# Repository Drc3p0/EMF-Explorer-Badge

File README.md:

# EMF Explorer Badge

Explore the electromagnetic frequencies around you with the [EMF Explorer badge](https://emfexplorer.space), created by Darcy Neal of [SporkLogic](https://sporklogic.com).

The EMF Explorer badge is ideal for soldering workshops at large-scale hacker camps. It aims to provide an accessible tool to inspire curiosity about electronics, and is designed to be easy to assemble by anyone who can wield a soldering iron. Assembly typically takes about one hour. 

## Assembly Instructions
Text, picture, and video assembly guide available at [https://emfexplorer.space/docs.html](https://emfexplorer.space/docs.html) 

## Learn how it Works
Check out the soundwalk videos, learning guides, zine, and frequency monitor at [https://emfexplorer.space/demos.html](https://emfexplorer.space/demos.html)

## Where to Buy
- Buy a ready-to-assemble kit from:
  - [MakerShed (US)](https://www.makershed.com/collections/all/products/emf)
  - [iFixit (US)](https://www.ifixit.com/products/emf-explorer-kit)
  - [Pimoroni (UK)](https://shop.pimoroni.com/en-us/products/emf-explorer-badge)
- Order a bare PCB from [OshPark](https://oshpark.com/shared_projects/bRVDS1Pq)
- Learn how to build your own from scratch in [MAKE Magazine, Vol 90](https://www.makershed.com/products/make-magazine-volume-90-print?pr_prod_strat=jac&pr_rec_id=abdde9ae7&pr_rec_pid=10507909955777&pr_ref_pid=10481106288833&pr_seq=uniform). 

## Project Info
This repo contains the design files for V1. [Videos of the EMF board in action](https://youtube.com/playlist?list=PLv4aAZ9vybC-C60QNva_aFFxgQik_hsGD&si=QTph-GFbRsYseA82)

## Inspiration
This project was born out of a drive to create accessible learning devices to teach students about electricity.  Some resources that proved invaluable in this process:
- [EMF amplifier workshop from eTextile Summer Camp 2016](https://etextile-summercamp.org/2016/emf/)
- [The legendary Elektrosluch](https://github.com/LOM-instruments/Elektrosluch-3/tree/master/hardware)
- [Gingerbread SVG to KiCad PCB art tool](https://gingerbread.wntr.dev/help.html)

## Images

Special edition purple PCB, courtesy of [OshPark](https://oshpark.com), used for workshops at the Open Hardware Summit '24 and dadaLab '24: 

## License

 <p xmlns:cc="http://creativecommons.org/ns#" >This work is licensed under <a href="https://creativecommons.org/licenses/by-nc-sa/4.0/?ref=chooser-v1" target="_blank" rel="license noopener noreferrer" style="display:inline-block;">CC BY-NC-SA 4.0</a></p>

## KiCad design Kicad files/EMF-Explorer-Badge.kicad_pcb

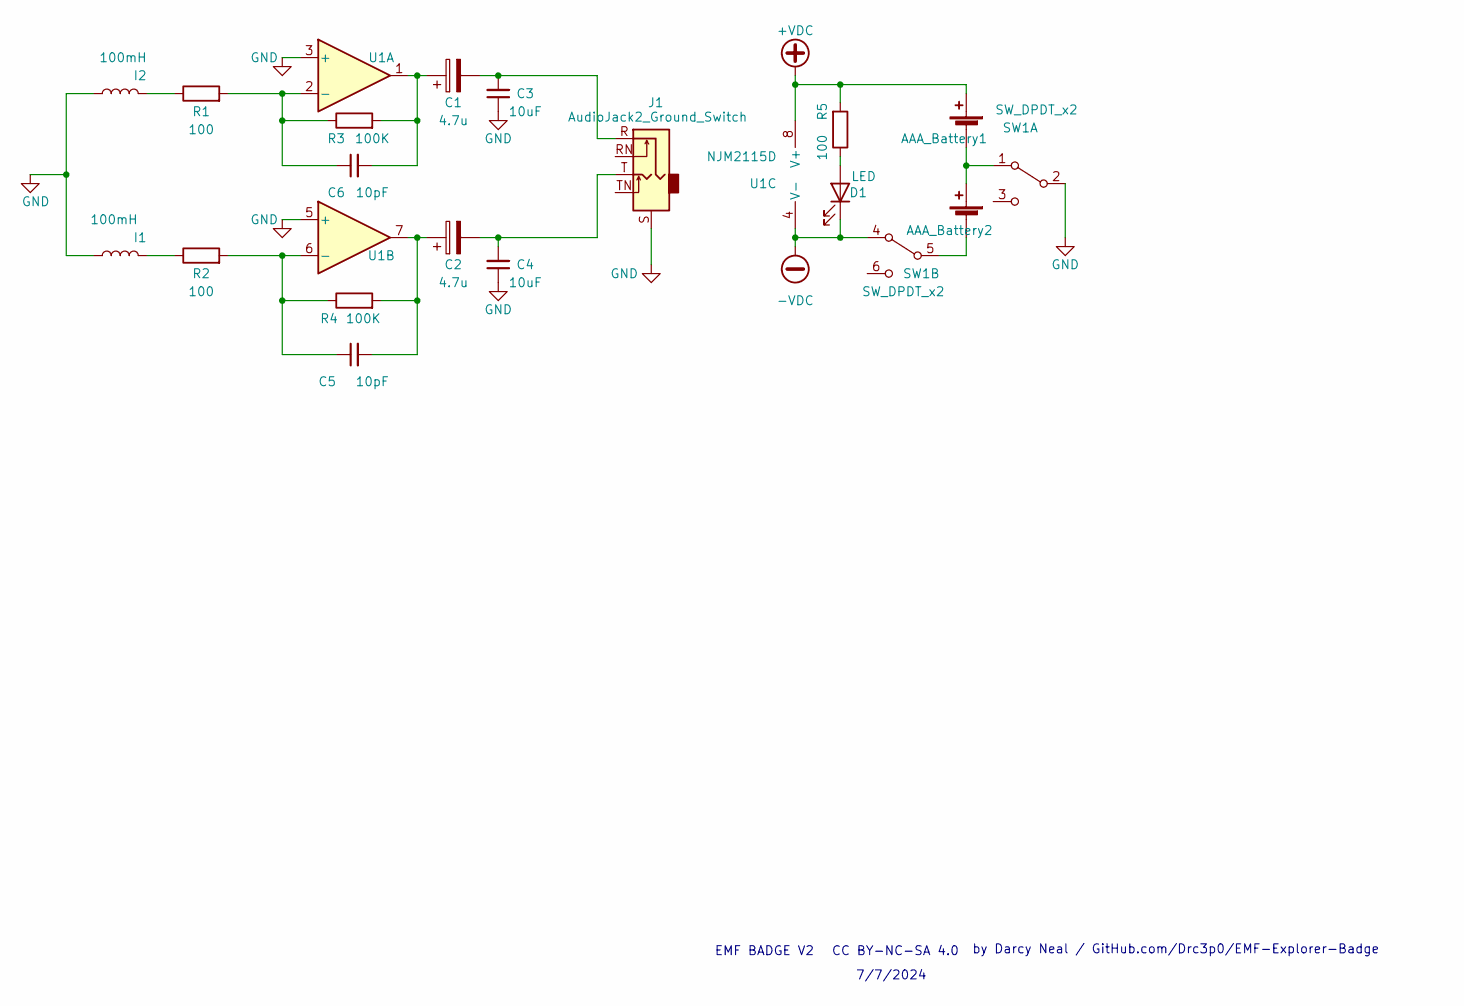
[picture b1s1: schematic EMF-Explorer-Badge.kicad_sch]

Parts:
AAA_Battery1: Spring_side->; BatteryHolder_Keystone_2466_1xAAA
AAA_Battery2: <-Spring_side; BatteryHolder_Keystone_2466_1xAAA
C1, C2: 4.7u; CP_Radial_D4.0mm_P2.54mm
C3, C4: 10uF; C_Disc_D4.3mm_W1.9mm_P5.00mm
C5, C6: 10pF; C_Disc_D3.4mm_W2.1mm_P2.50mm
D1: LED; LED_D5.0mm_Horizontal_O1.27mm_Z9.0mm
I1, I2: 100mH; Inductor_D5.0mm_Horizontal_O3.81mm_Z9.0mm
J1: AudioJack2_Ground_Switch; Jack_3.5mm_CUI_SJ1-3525N_Horizontal
R1, R2, R5: 100; R_Axial_DIN0207_L6.3mm_D2.5mm_P7.62mm_Horizontal
R3, R4: 100K; R_Axial_DIN0207_L6.3mm_D2.5mm_P7.62mm_Horizontal
SW1: SW_DPDT_x2; DPDT slide switch
U1: NJM2115D; DIP-8_W7.62mm

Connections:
+VDC: AAA_Battery1.1 (+), R5.2, U1.8 (V+)
-VDC: D1.1 (K), SW1.4 (A), U1.4 (V-)
GND: C3.1, C4.1, I1.1, I2.1, J1.S, SW1.2 (B), U1.3 (+), U1.5 (+)
unnamed: AAA_Battery1.2 (-), AAA_Battery2.1 (+), SW1.1 (A)
unnamed: AAA_Battery2.2 (-), SW1.5 (B)
unnamed: C1.1, C6.2, R3.2, U1.1
unnamed: C1.2, C3.2, J1.R
unnamed: C2.1, C5.2, R4.2, U1.7
unnamed: C2.2, C4.2, J1.T
unnamed: D1.2 (A), R5.1
unnamed: I1.2, R2.1
unnamed: I2.2, R1.1
unnamed: C6.1, R1.2, R3.1, U1.2 (-)
unnamed: C5.1, R2.2, R4.1, U1.6 (-)

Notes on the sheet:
EMF BADGE V2
CC BY-NC-SA 4.0
by Darcy Neal / GitHub.com/Drc3p0/EMF-Explorer-Badge
7/7/2024

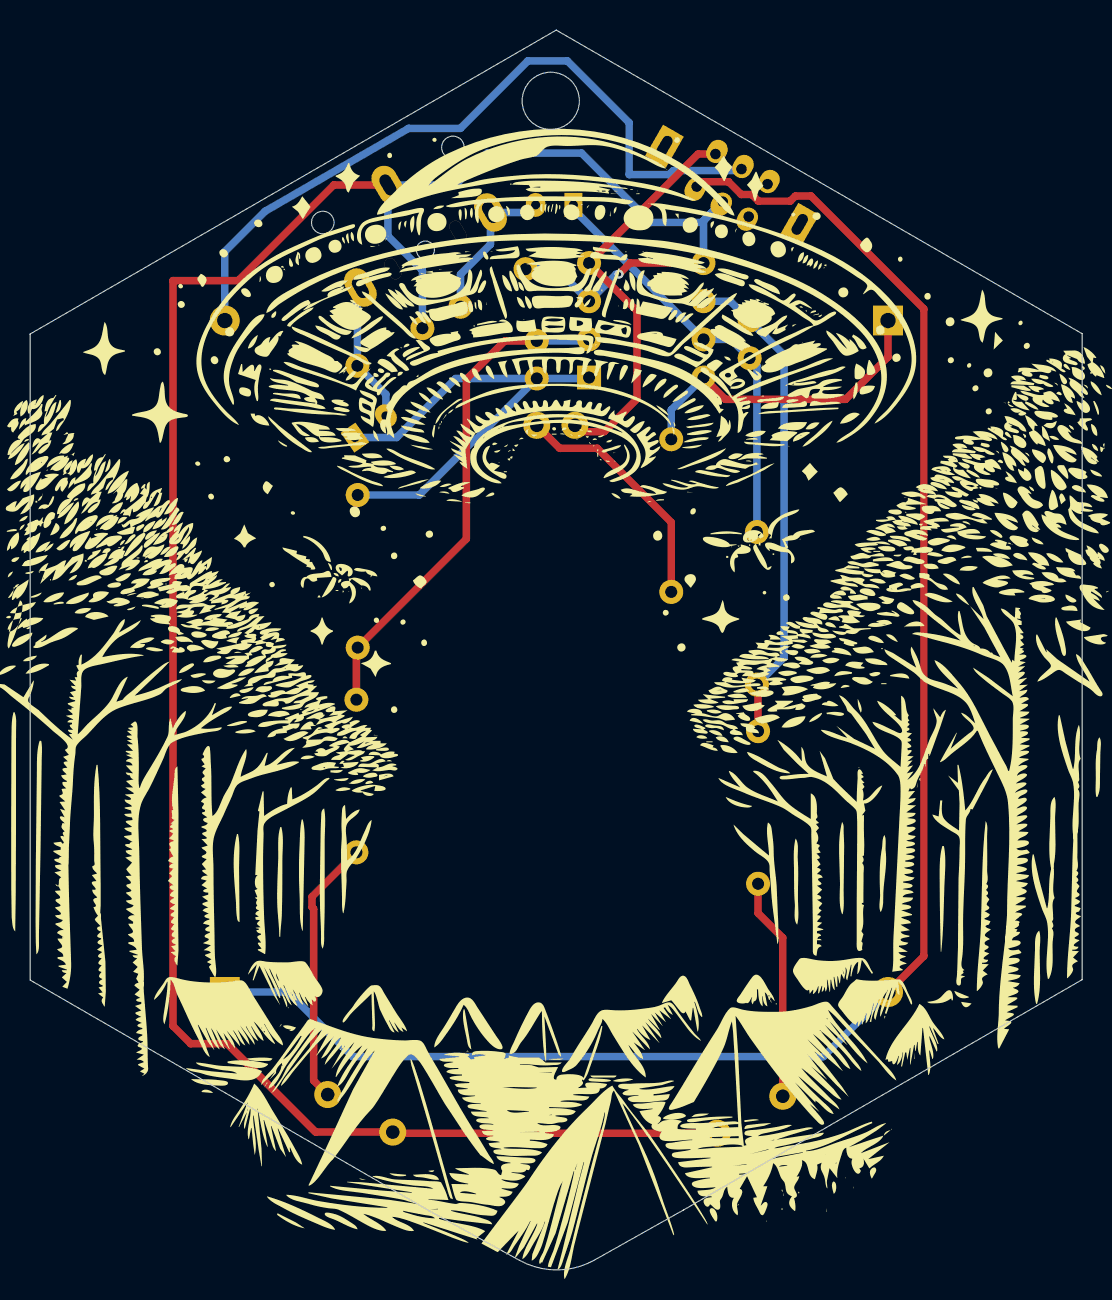
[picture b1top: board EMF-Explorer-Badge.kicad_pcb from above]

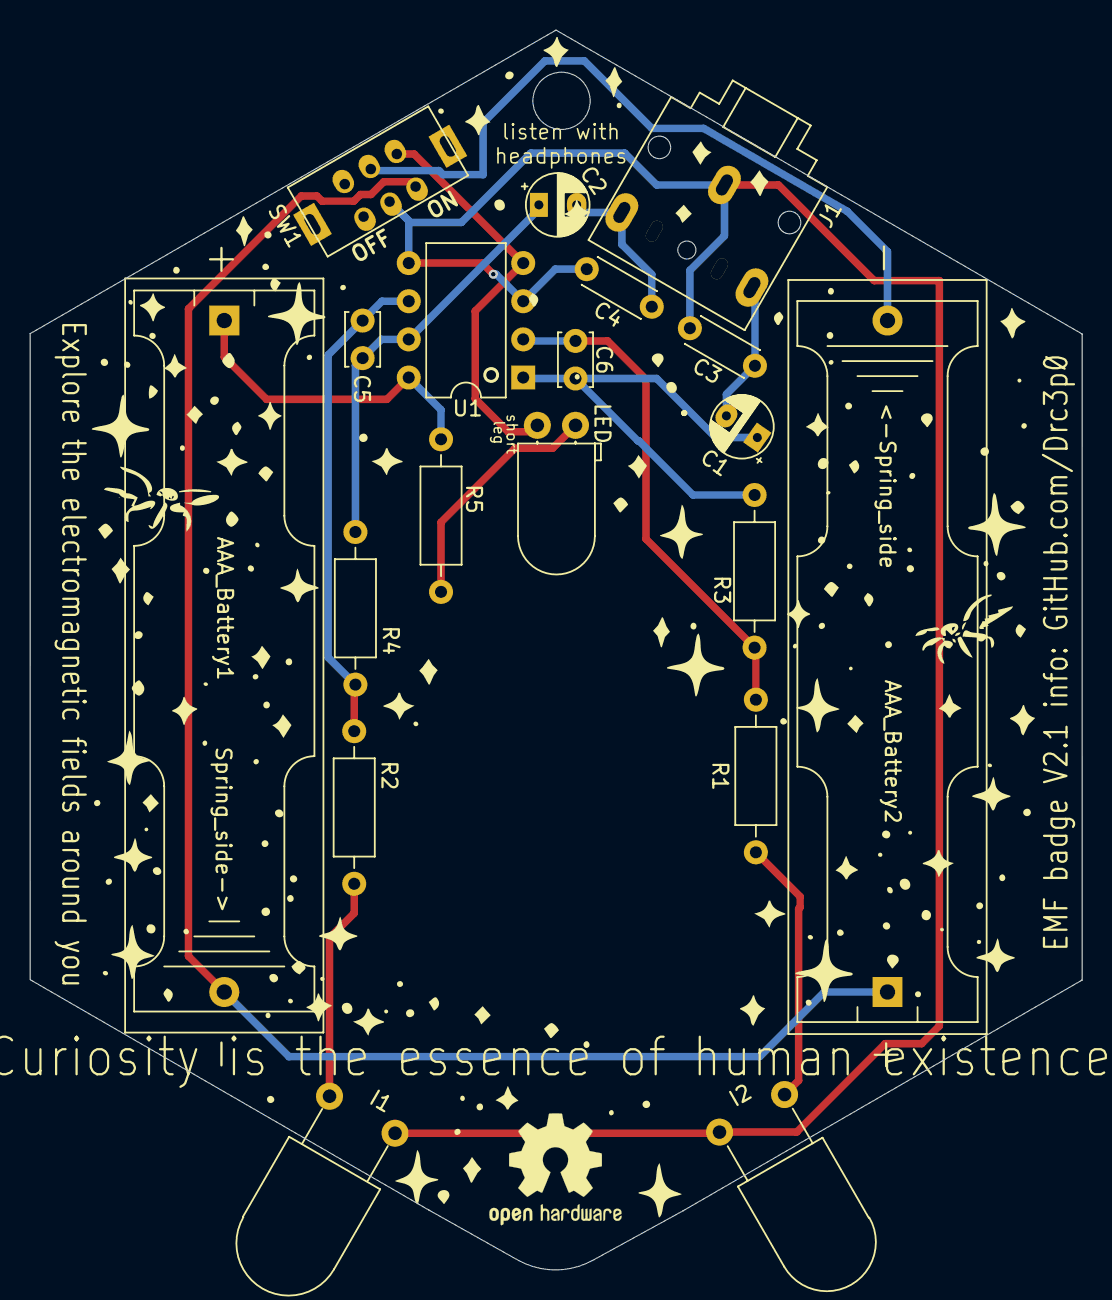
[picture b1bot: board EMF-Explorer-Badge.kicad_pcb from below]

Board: 2 copper layers, 70.0 x 82.5 mm, 19 parts (19 on the bottom side), 14 nets.

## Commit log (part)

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2024-04-26 file cleanup
2024-07-19 file uploads
2024-07-19 Rename PXL_20240711_210140224.jpg to EMFboardsFloral.jpg
2024-10-05 Update README.md
    update Makershed url
2025-12-23 Fix assembly guide link and wording in README
    Updated the assembly guide link and corrected the wording for time estimation.
2025-12-23 Fix links and formatting in README.md
2025-12-23 Update README to include SporkLogic attribution
    Added attribution to SporkLogic in the project description.
2026-06-04 Kicad 9 file cleanup
